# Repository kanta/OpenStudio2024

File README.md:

# OPEN HOME OPEN STUDIO 2024

[堀尾寛太](https://horiokanta.com/)の作業場と自宅が一体となって長野県佐久市に移転して1年ちょっと。依然として全体的に何かの途中という状態ですが、家と作業場どちらもオープンという会を行います。

## 基本情報
- 日時： 2024年4月13日（土）13:00-16:00
- 会場： 堀尾スタジオ＆堀尾家（[長野県佐久市岩村田上ノ城](https://maps.app.goo.gl/3SL8g3zoJbbMY6ZR9)）
  - 個人宅につき、参加登録された方に住所とアクセス方法をお知らせいたします。
- 入場無料
- [気温](https://docs.google.com/spreadsheets/d/1d41NWnKz_-3gai1RPzNCwqmcrNDzAIPshY2XLD4peys/edit?usp=sharing)
 
## 内容（見込み）
- 新作インスタレーションの展示
- 過去作復刻展示
- 作品にも製品にもなっていない試作品の展示
- 別名義「[ポノール・エクスペリメンツ](https://ponoor.com/)」の紹介
- やりかけDIYリフォームの現場を眺める
- ご近所のミニ散歩ツアー
- ガレージセール
- キッズコーナー

## 参加登録
[こちらのフォーム](https://docs.google.com/forms/d/1lhzb7XwlRHWgd9XNmenYOhGv0y0wSqm278sAvCR6YCc/edit)から登録をお願いします。

お願い：スリッパが不足しそうですので、もし持ってこれる方は持参いただけますと助かります。床は合板のままの部分があり、靴下や素足だととげが刺さる可能性があります。あと当日の気温によってはスリッパがないと寒いかもしれません。

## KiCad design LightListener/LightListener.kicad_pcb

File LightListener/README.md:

# Stereo Light Receiver
- [Schematic](https://github.com/kanta/OpenStudio2024/blob/main/LightListener/schematic.pdf) (回路図)
- [BOM](https://docs.google.com/spreadsheets/d/10PK1covkURqqtIWLEjVXwmHwA0KFT7VGd_VK9LacYOU/edit?usp=sharing) (部品表)
- [Housing 3D data](https://a360.co/4415aBl)

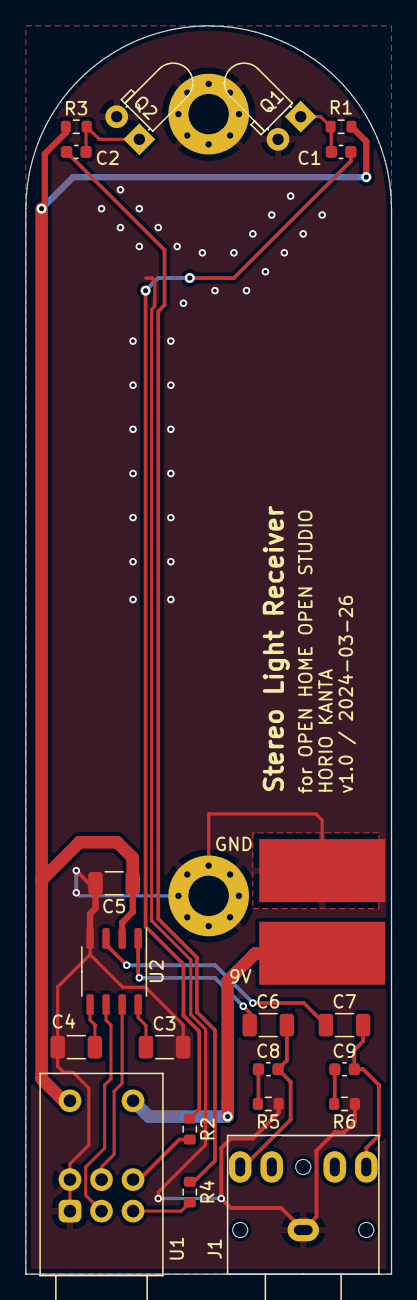
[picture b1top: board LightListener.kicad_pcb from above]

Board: 2 copper layers, 29.0 x 99.0 mm, 24 parts (0 on the bottom side), 19 nets.

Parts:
C1, C2: 47nF; C_0603_1608Metric
C3, C4, C5, C6, C7: 100uF; C_1206_3216Metric
C8, C9: 100nF; C_0603_1608Metric
H1, H2: MountingHole_Pad; MountingHole_3.2mm_M3_Pad_Via
J1: AudioJack3_SwitchTR; MJ-495A
J2, J3: Conn_01x01; SolderWirePad_1x01_SMD_5x10mm
Q1, Q2: Q_Photo_NPN; LED_D3.0mm_Horizontal_O1.27mm_Z2.0mm_IRBlack
R1, R3: 10k; R_0603_1608Metric
R2, R4: 100k; R_0603_1608Metric
R5, R6: 4.7; R_0603_1608Metric
U1: Potentiometer_Alps_RK097_Dual_Horizontal_Switch
U2: TDA2822G-S08; SOP-8_3.9x4.9mm_P1.27mm

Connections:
GND: C3.2, C4.2, C5.2, H1.1, H2.1, J1.S, J3.1, Q1.2 (E), Q2.2 (E), R5.1, R6.1, U1.1, U1.4, U2.4 (GND)
unnamed: C1.2, R2.1
unnamed: C2.2, R4.1
unnamed: C6.2, C8.2, J1.T
unnamed: C7.2, C9.2, J1.R
unnamed: C8.1, R5.2
unnamed: C9.1, R6.2
unnamed: J2.1, U1.8 (B)
unnamed: C1.1, Q1.1 (C), R1.2
unnamed: C2.1, Q2.1 (C), R3.2
unnamed: R2.2, U1.6
unnamed: R4.2, U1.3
unnamed: U1.5, U2.7 (IN1)
unnamed: U1.2, U2.6 (IN2)
unnamed: C3.1, U2.8 (NP1)
unnamed: C4.1, U2.5 (NP2)
unnamed: C6.1, U2.1 (OUT1)
unnamed: C7.1, U2.3 (OUT2)
VCC: C5.1, R1.1, R3.1, U1.7 (A), U2.2 (VCC)

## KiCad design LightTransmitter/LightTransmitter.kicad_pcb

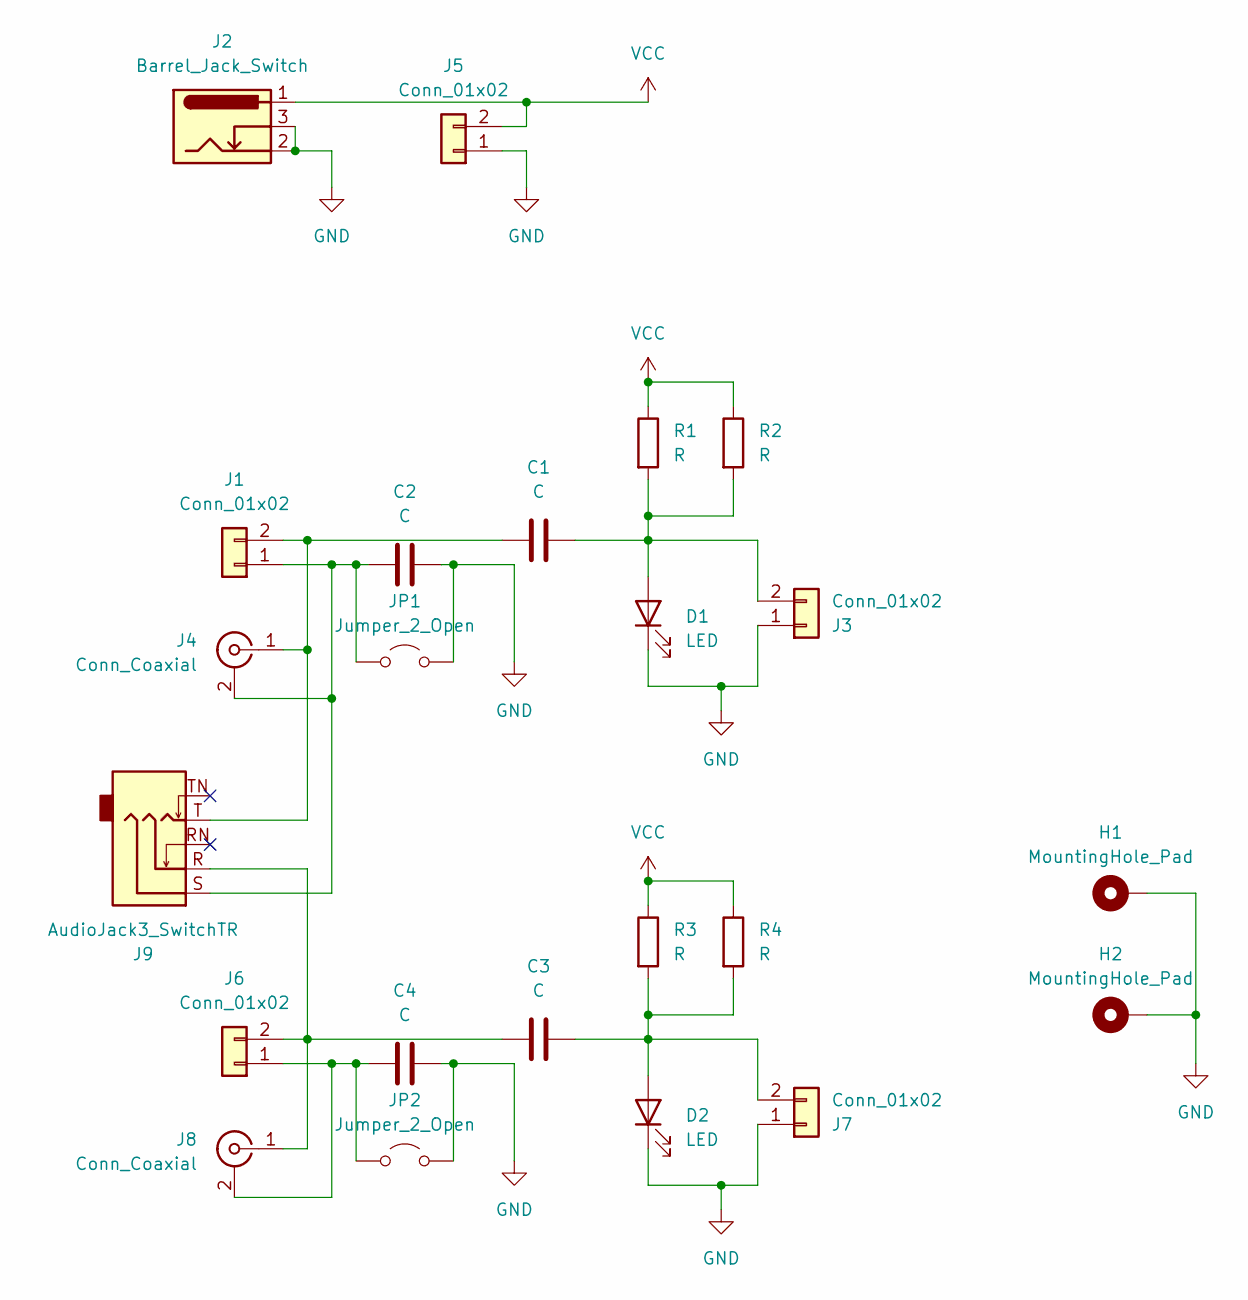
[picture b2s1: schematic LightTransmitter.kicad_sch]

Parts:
C1, C2, C3, C4: C; C_1210_3225Metric_Pad1.33x2.70mm_HandSolder
D1, D2: LED; LED_D5.0mm_Horizontal_O1.27mm_Z9.0mm
H1, H2: MountingHole_Pad; MountingHole_3.2mm_M3_DIN965_Pad
J1, J3, J5, J6, J7: Conn_01x02; PhoenixContact_MCV_1,5_2-G-3.81_1x02_P3.81mm_Vertical
J2: Barrel_Jack_Switch; BarrelJack_Horizontal
J4, J8: Conn_Coaxial; MJ-523
J9: AudioJack3_SwitchTR; MJ-495A
JP1, JP2: Jumper_2_Open; SolderJumper-2_P1.3mm_Open_RoundedPad1.0x1.5mm
R1, R3: R; R_Axial_Power_L25.0mm_W9.0mm_P30.48mm
R2, R4: R; R_Axial_DIN0309_L9.0mm_D3.2mm_P12.70mm_Horizontal

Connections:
GND: C2.2, C4.2, D1.1 (K), D2.1 (K), H1.1, H2.1, J2.2, J2.3, J3.1, J5.1, J7.1, JP1.2 (B), JP2.2 (B)
unnamed: C1.2, D1.2 (A), J3.2, R1.2, R2.2
unnamed: C3.2, D2.2 (A), J7.2, R3.2, R4.2
unnamed: C2.1, J1.1, J4.2 (Ext), J9.S, JP1.1 (A)
unnamed: C1.1, J1.2, J4.1 (In), J9.T
unnamed: C4.1, J6.1, J8.2 (Ext), JP2.1 (A)
unnamed: C3.1, J6.2, J8.1 (In), J9.R
VCC: J2.1, J5.2, R1.1, R2.1, R3.1, R4.1

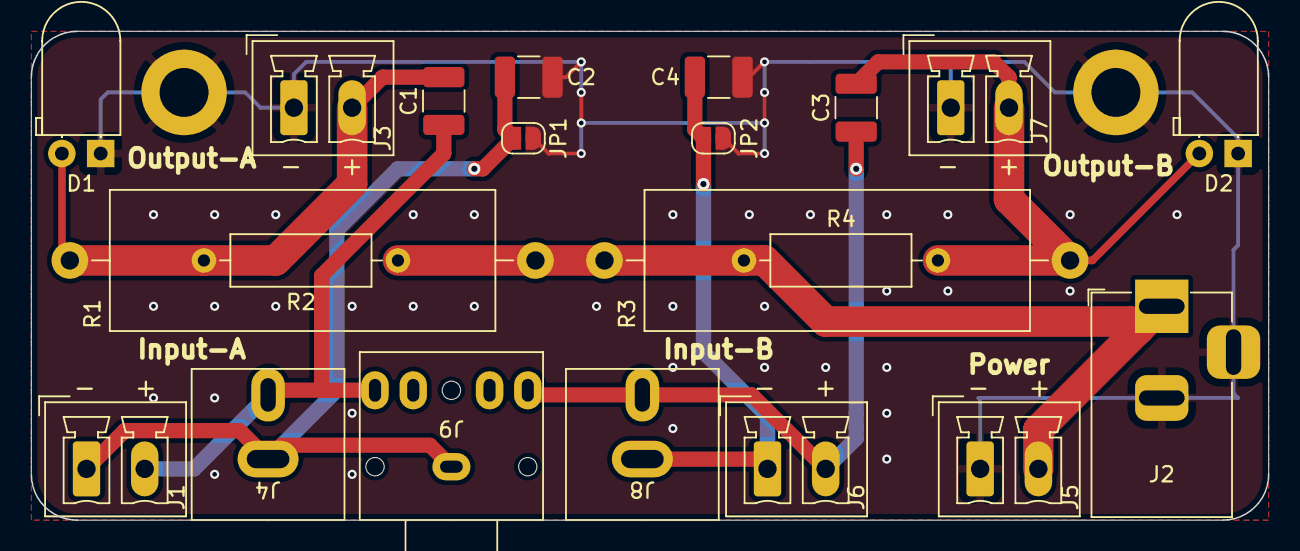
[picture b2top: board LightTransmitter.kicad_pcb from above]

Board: 2 copper layers, 81.0 x 32.0 mm, 23 parts (0 on the bottom side), 8 nets.

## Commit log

2024-03-09 start the schematic
2024-03-15 earphone amplifier
2024-03-18 footprint assignment
2024-03-24 PCB design (brief)
2024-03-25 Update README.md
    added the temperature log
2024-03-27 transmitter pcb design
2024-04-09 Changed some resistance and capacitance values
2024-04-13 housing 3d data
2024-04-15 Organize schematics.
